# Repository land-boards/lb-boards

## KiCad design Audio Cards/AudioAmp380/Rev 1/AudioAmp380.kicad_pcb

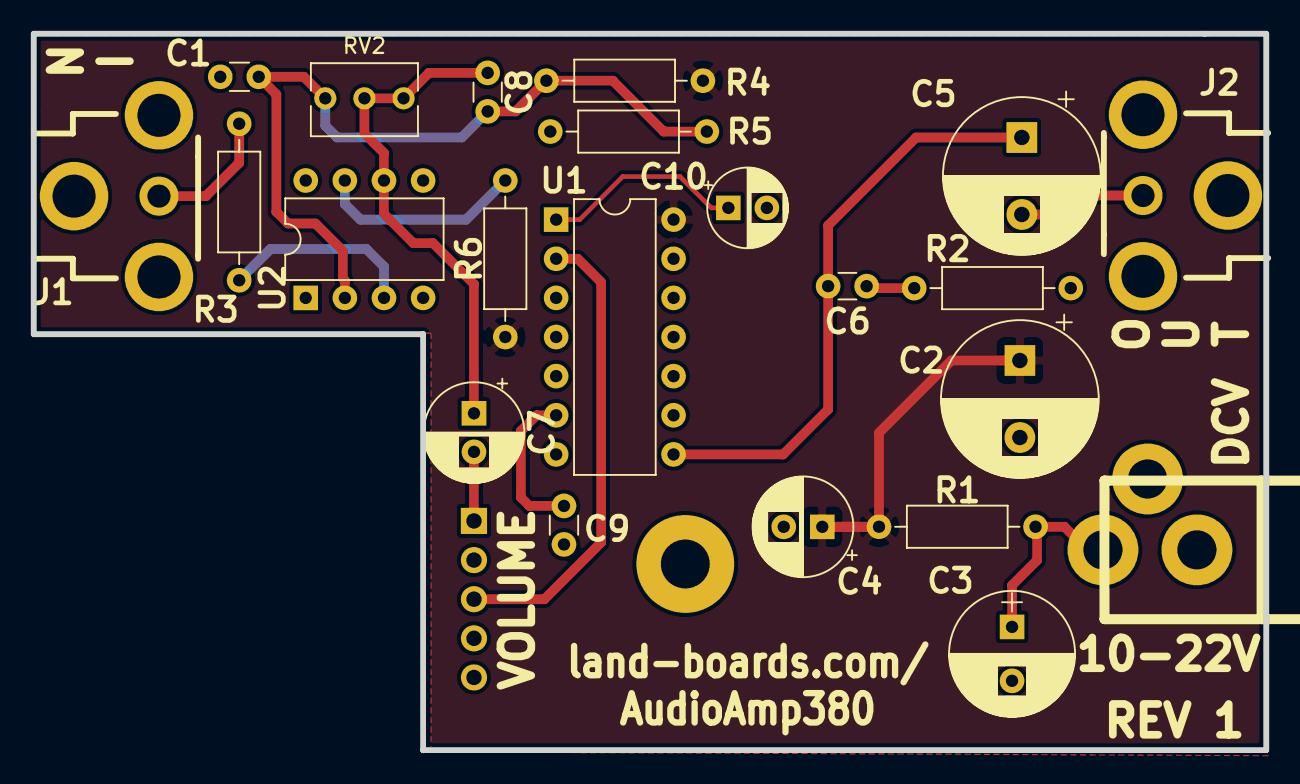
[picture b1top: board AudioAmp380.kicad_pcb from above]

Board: 2 copper layers, 80.0 x 46.5 mm, 25 parts (1 on the bottom side), 15 nets.

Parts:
C1, C8, C9: 0.1 uF; C_Disc_D3.0mm_W1.6mm_P2.50mm
C2, C5: 470uF; CP_Radial_D10.0mm_P5.00mm
C3: 100uF; CP_Radial_D8.0mm_P3.50mm
C4: 1 uF; CP_Radial_D6.3mm_P2.50mm
C6: 100uF; C_Disc_D3.0mm_W1.6mm_P2.50mm
C7: 10 uF; CP_Radial_D6.3mm_P2.50mm
C10: 4.7uF; CP_Radial_D5.0mm_P2.50mm
J1, J2: RCA-JACK; RCA
J3: DCJ0202; DCJ-NEW
MTG4: MTG_HOLE; MTG-4-40
R1, R6: 10; R_Axial_DIN0207_L6.3mm_D2.5mm_P10.16mm_Horizontal
R2: 2.7; R_Axial_DIN0207_L6.3mm_D2.5mm_P10.16mm_Horizontal
R3: 51; R_Axial_DIN0207_L6.3mm_D2.5mm_P10.16mm_Horizontal
R4, R5: 10K; R_Axial_DIN0207_L6.3mm_D2.5mm_P10.16mm_Horizontal
RV1: CONN_01X05; Pin_Header_Angled_1x05_Pitch2.54mm
RV2: 500; Potentiometer_Bourns_3266Y_Vertical
TESTED: COUPON; TEST_BLK-REAR
U1: LM380N; DIP-14_W7.62mm
U2: NE5534; DIP-8_W7.62mm

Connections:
/12VF: C2.1, C4.1, R1.1, R4.1, R6.1, U1.14
/+12V: C3.1, J3.1, R1.2
/AO: C5.1, C6.1, U1.8
/COMP: C6.2, R2.1
/IN: J1.4, R3.1
/OUT: C5.2, J2.4
/RESHI: C7.2, RV1.1
/RESWI: RV1.3, U1.2
GND: C1.2, C2.2, C3.2, C4.2, C9.1, C10.2, J1.1, J1.2, J1.3, J2.1, J2.2, J2.3, J3.2, J3.3, R2.2, R5.2, RV1.5, U1.3, U1.4, U1.5, U1.7, U1.10, U1.11, U1.12, U2.4
unnamed: C1.1, C8.2, R4.2, R5.1, RV2.3, U2.2
unnamed: C7.1, C8.1, RV2.1, RV2.2, U2.6
unnamed: C9.2, U1.6
unnamed: C10.1, U1.1
unnamed: R3.2, U2.3
unnamed: R6.2, U2.7

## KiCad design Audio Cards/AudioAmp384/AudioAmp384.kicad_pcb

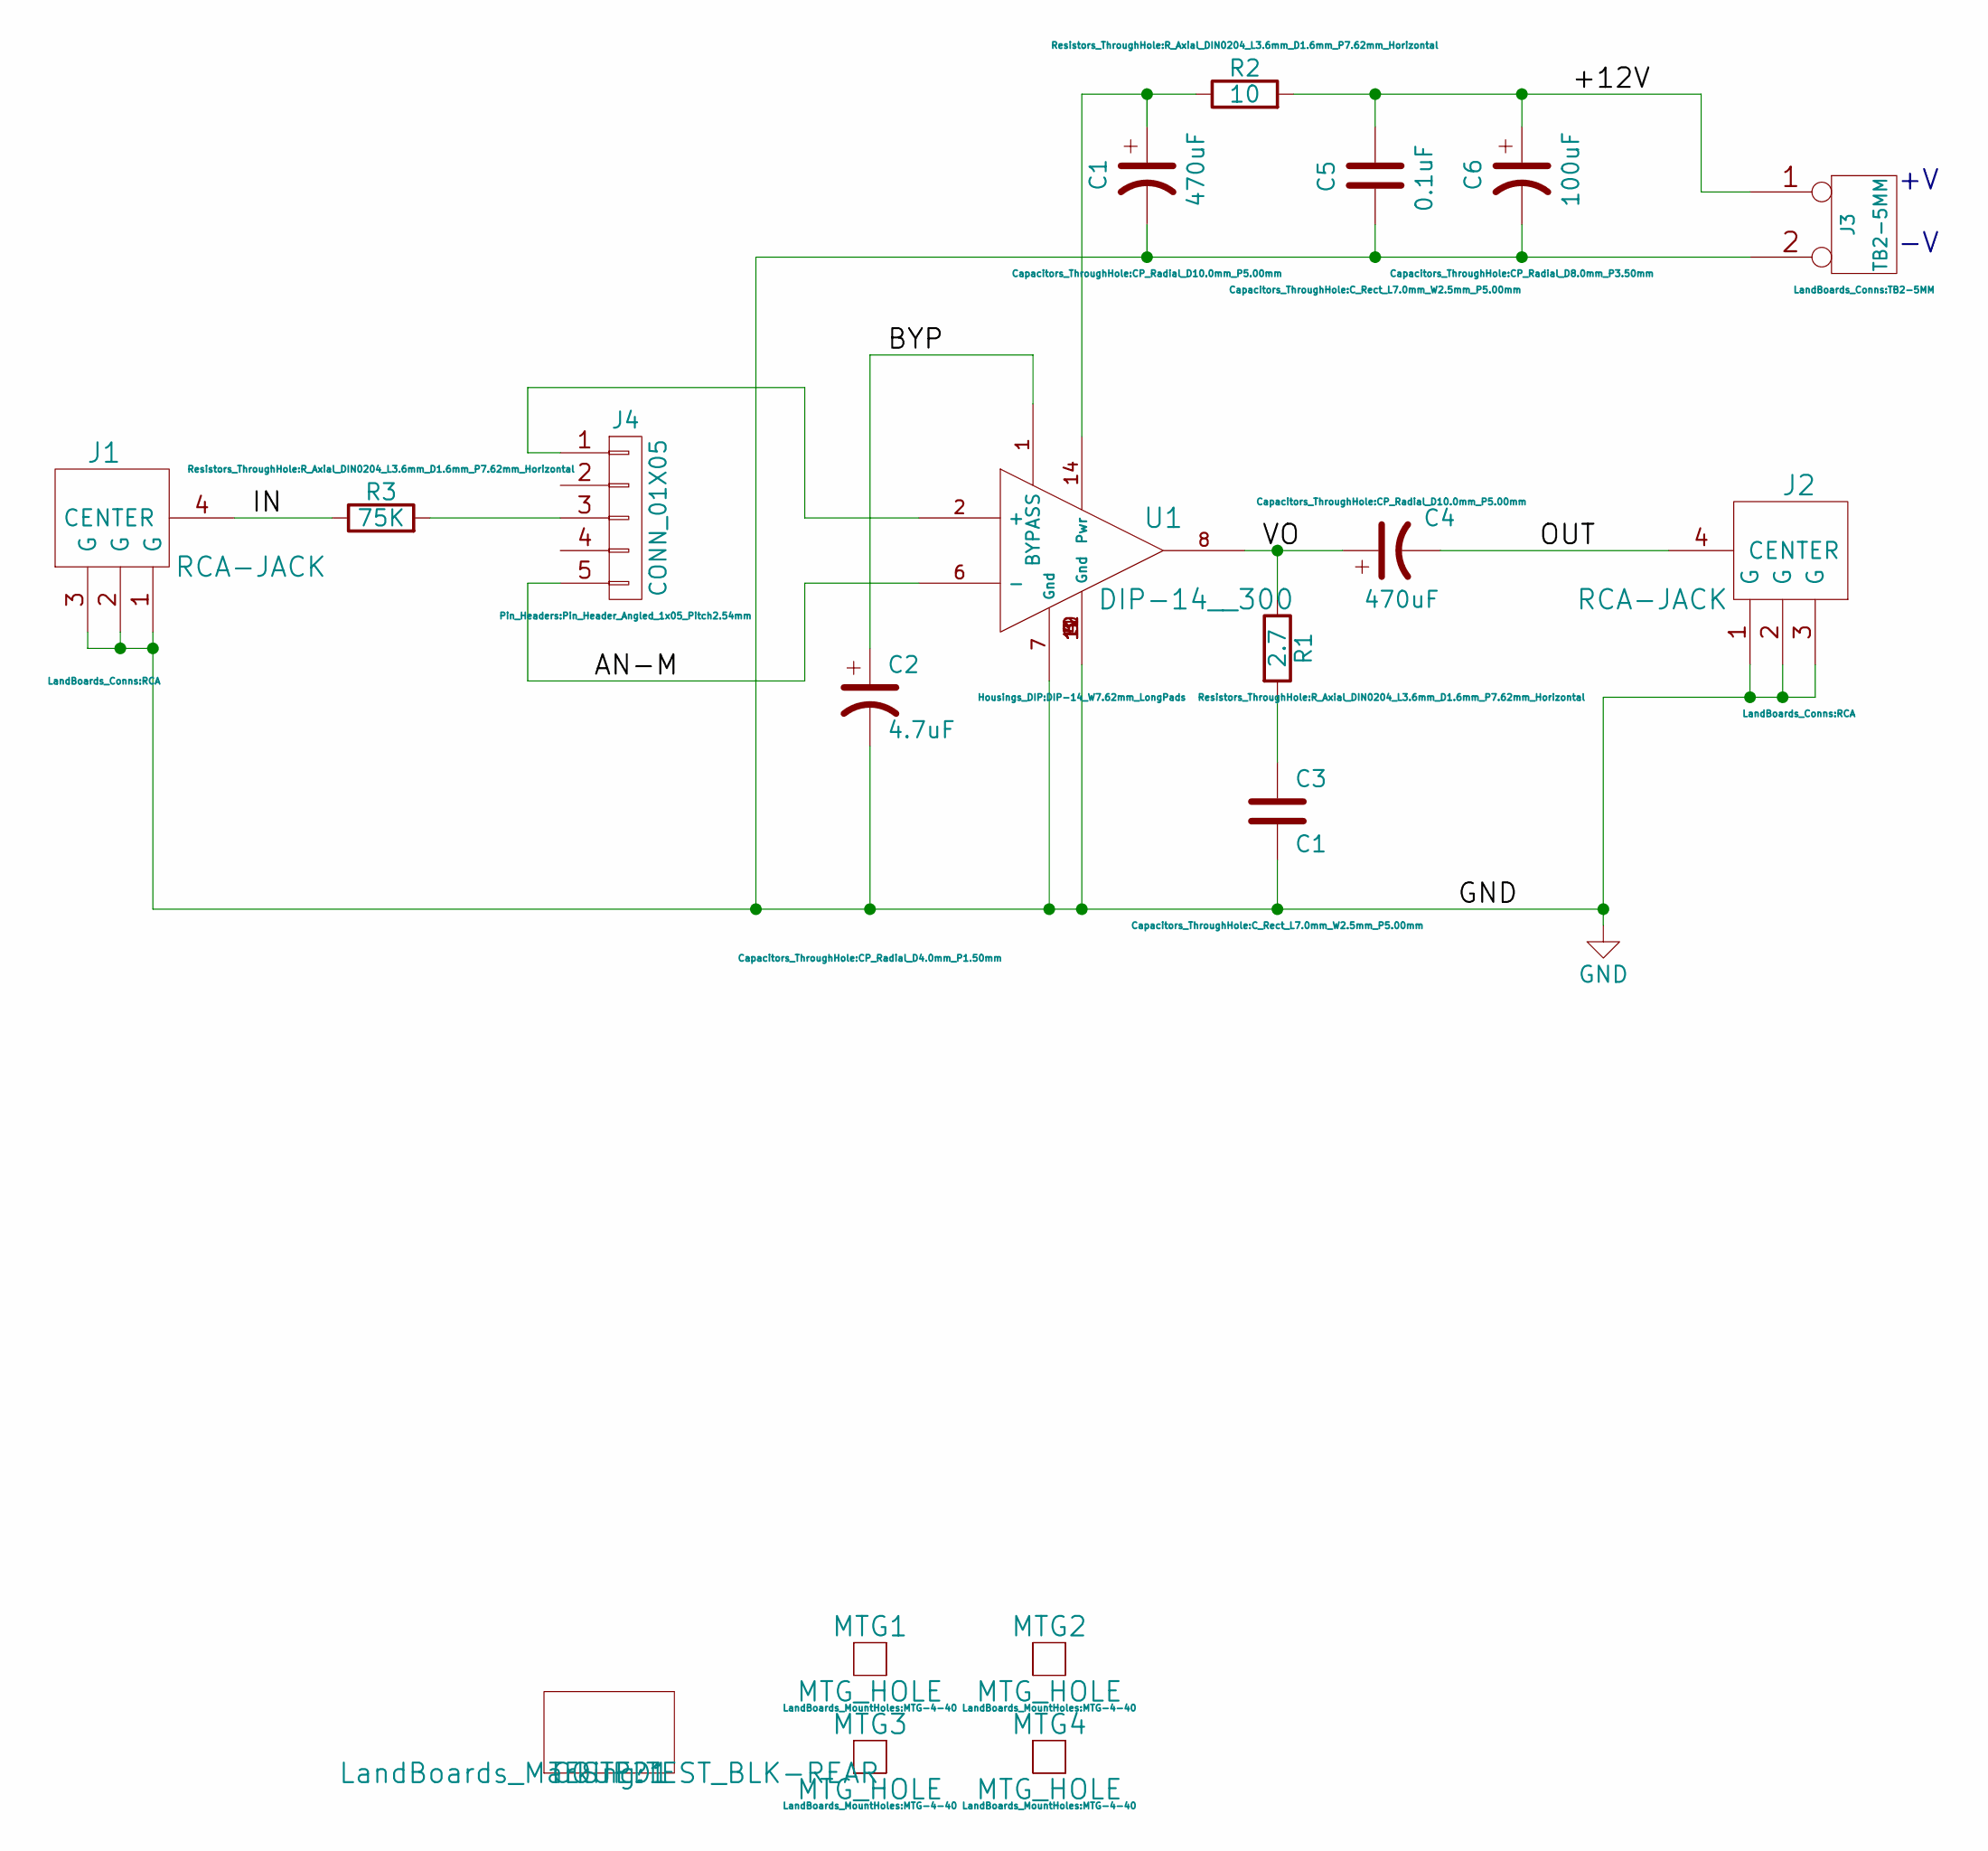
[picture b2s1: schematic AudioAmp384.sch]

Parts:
C1, C4: 470uF; CP_Radial_D10.0mm_P5.00mm
C2: 4.7uF; CP_Radial_D4.0mm_P1.50mm
C3: C1; C_Rect_L7.0mm_W2.5mm_P5.00mm
C5: 0.1uF; C_Rect_L7.0mm_W2.5mm_P5.00mm
C6: 100uF; CP_Radial_D8.0mm_P3.50mm
COUP?1: TESTED1; TEST_BLK-REAR
J1, J2: RCA-JACK; RCA
J3: TB2-5MM
J4: CONN_01X05; Pin_Header_Angled_1x05_Pitch2.54mm
MTG1, MTG2, MTG3, MTG4: MTG_HOLE; MTG-4-40
R1: 2.7; R_Axial_DIN0204_L3.6mm_D1.6mm_P7.62mm_Horizontal
R2: 10; R_Axial_DIN0204_L3.6mm_D1.6mm_P7.62mm_Horizontal
R3: 75K; R_Axial_DIN0204_L3.6mm_D1.6mm_P7.62mm_Horizontal
U1: DIP-14__300; DIP-14_W7.62mm_LongPads

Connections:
/+12V: C5.2, C6.1, J3.1, R2.2
/AN-M: J4.5, U1.6 (-)
/BYP: C2.1, U1.1 (BYPASS)
/IN: J1.4 (CENTER), R3.1
/OUT: C4.2, J2.4 (CENTER)
/VO: C4.1, R1.1, U1.8
GND: C1.2, C2.2, C3.2, C5.1, C6.2, J1.1 (G), J1.2 (G), J1.3 (G), J2.1 (G), J2.2 (G), J2.3 (G), J3.2 (PM), U1.3 (Gnd), U1.4 (Gnd), U1.5 (Gnd), U1.7 (Gnd), U1.10 (Gnd), U1.11 (Gnd), U1.12 (Gnd)
unnamed: C1.1, R2.1, U1.14 (Pwr)
unnamed: C3.1, R1.2
unnamed: J4.1, U1.2 (+)
unnamed: J4.3, R3.2

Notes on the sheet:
+V -V

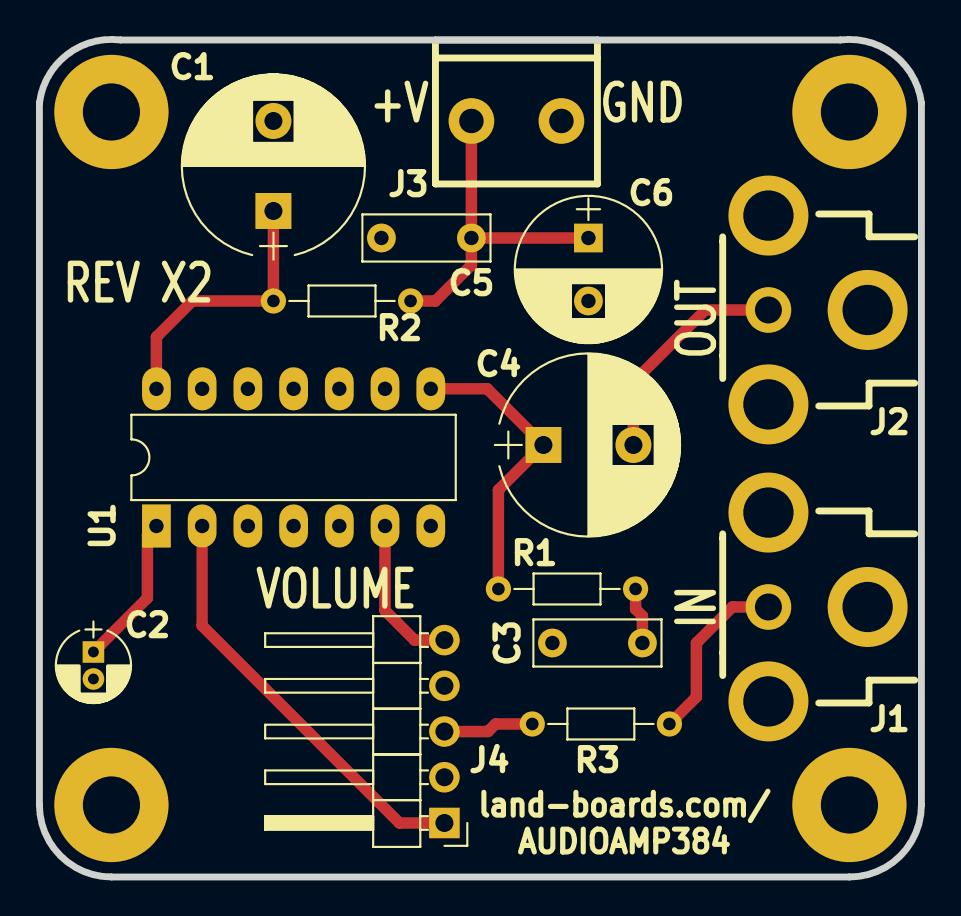
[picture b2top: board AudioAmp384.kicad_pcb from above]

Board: 2 copper layers, 49.0 x 46.5 mm, 19 parts (0 on the bottom side), 11 nets.

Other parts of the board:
TESTED: TESTED1; TEST_BLK-REAR

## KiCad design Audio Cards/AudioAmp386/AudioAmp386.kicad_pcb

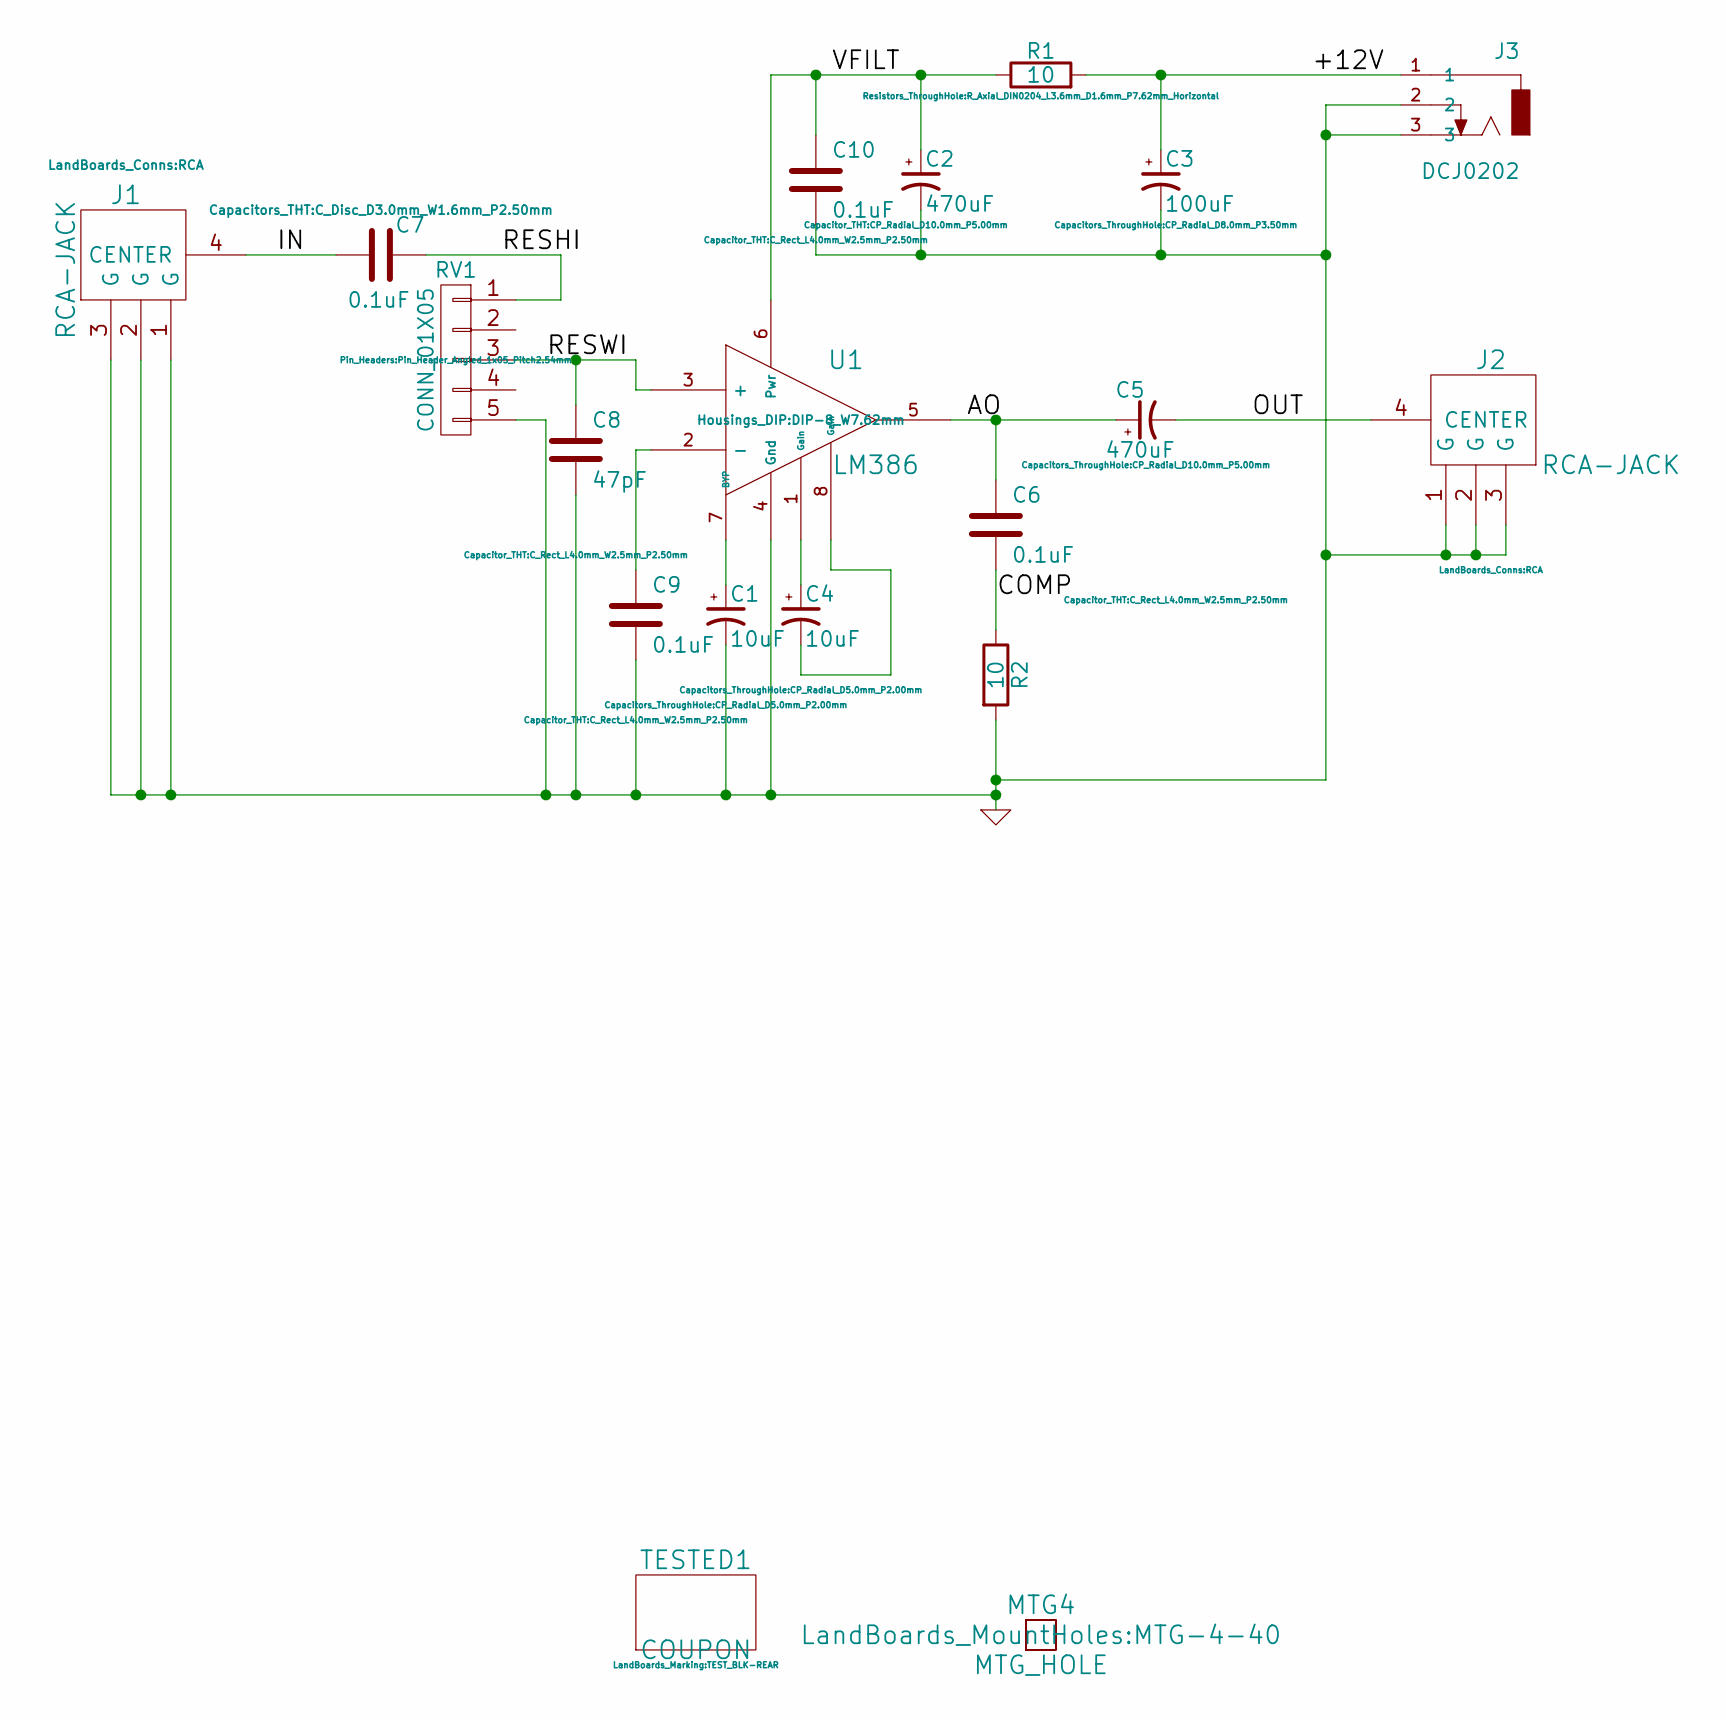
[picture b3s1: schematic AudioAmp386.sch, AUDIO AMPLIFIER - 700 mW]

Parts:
C1, C4: 10uF; CP_Radial_D5.0mm_P2.00mm
C2, C5: 470uF; CP_Radial_D10.0mm_P5.00mm
C3: 100uF; CP_Radial_D8.0mm_P3.50mm
C6, C9, C10: 0.1uF; C_Rect_L4.0mm_W2.5mm_P2.50mm
C7: 0.1uF; C_Disc_D3.0mm_W1.6mm_P2.50mm; MfgPN 1C10Z5U104M050B
C8: 47pF; C_Rect_L4.0mm_W2.5mm_P2.50mm
J1, J2: RCA-JACK; RCA; MfgPN NYS354
J3: DCJ0202; DCJ-NEW
MTG4: MTG_HOLE; MTG-4-40
R1: 10; R_Axial_DIN0204_L3.6mm_D1.6mm_P7.62mm_Horizontal
R2: 10; R_Axial_DIN0204_L3.6mm_D1.6mm_P7.62mm_Horizontal; MfgPN CCF0710R0GKE36
RV1: CONN_01X05; Pin_Header_Angled_1x05_Pitch2.54mm
TESTED1: COUPON; TEST_BLK-REAR
U1: LM386; DIP-8_W7.62mm; MfgPN LM386N-3/NOPB

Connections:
/+12V: C3.1, J3.1, R1.2
/AO: C5.1, C6.1, U1.5
/COMP: C6.2, R2.1
/IN: C7.1, J1.4 (CENTER)
/OUT: C5.2, J2.4 (CENTER)
/RESHI: C7.2, RV1.1
/RESWI: C8.1, RV1.3, U1.3 (+)
/VFILT: C2.1, C10.1, R1.1, U1.6 (Pwr)
GND: C1.2, C2.2, C3.2, C8.2, C9.2, C10.2, J1.1 (G), J1.2 (G), J1.3 (G), J2.1 (G), J2.2 (G), J2.3 (G), J3.2, J3.3, R2.2, RV1.5, U1.4 (Gnd)
unnamed: C1.1, U1.7 (BYP)
unnamed: C4.1, U1.1 (Gain)
unnamed: C4.2, U1.8 (Gain)
unnamed: C9.1, U1.2 (-)

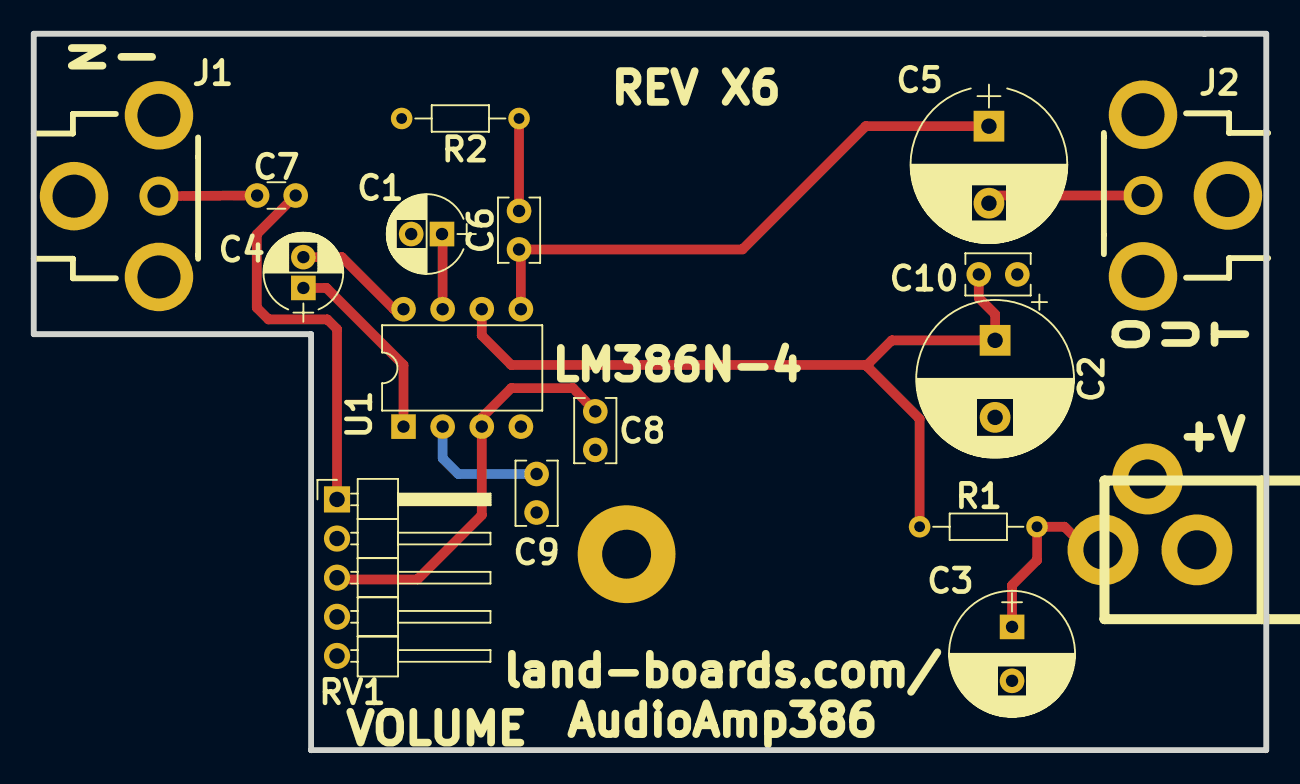
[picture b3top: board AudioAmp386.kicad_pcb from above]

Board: 2 copper layers, 80.0 x 46.5 mm, 19 parts (0 on the bottom side), 13 nets.

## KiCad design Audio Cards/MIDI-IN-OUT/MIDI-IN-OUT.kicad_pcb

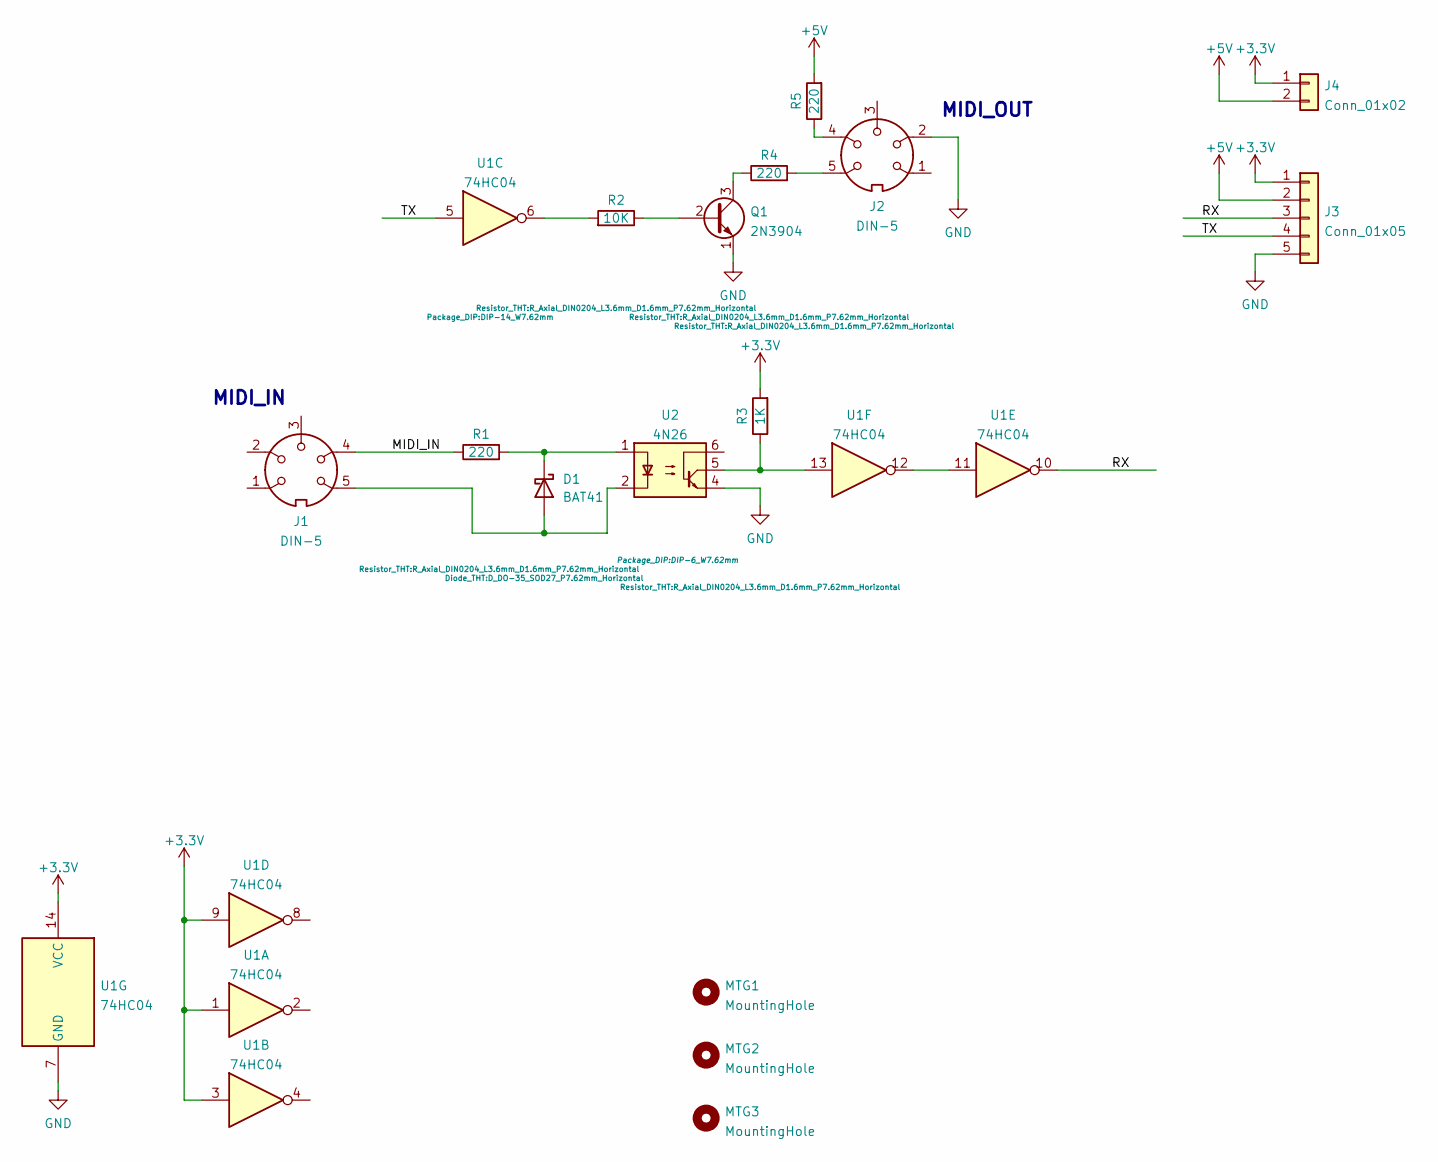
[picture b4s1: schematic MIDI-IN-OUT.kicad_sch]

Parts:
D1: BAT41; D_DO-35_SOD27_P7.62mm_Horizontal
J1, J2: DIN-5; MIDI_DIN-5
J3: Conn_01x05; PinHeader_1x05_P2.54mm_Horizontal
J4: Conn_01x02; PinHeader_1x02_P2.54mm_Vertical
MTG1, MTG2, MTG3: MountingHole; MTG-4-40-SMALL
Q1: 2N3904; TO-92_Inline
R1, R4, R5: 220; R_Axial_DIN0204_L3.6mm_D1.6mm_P7.62mm_Horizontal
R2: 10K; R_Axial_DIN0204_L3.6mm_D1.6mm_P7.62mm_Horizontal
R3: 1K; R_Axial_DIN0204_L3.6mm_D1.6mm_P7.62mm_Horizontal
U1: 74HC04
U2: 4N26; DIP-6_W7.62mm

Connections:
+3V3: J3.1, J4.1, R3.2, U1.1, U1.3, U1.9, U1.14 (VCC)
+5V: J3.2, J4.2, R5.2
/MIDI_IN: J1.4, R1.1
/RX: J3.3, U1.10
/TX: J3.4, U1.5
GND: J2.2, J3.5, Q1.1 (E), U1.7 (GND), U2.4
unnamed: D1.1 (K), R1.2, U2.1
unnamed: D1.2 (A), J1.5, U2.2
unnamed: J2.4, R5.1
unnamed: J2.5, R4.2
unnamed: Q1.2 (B), R2.1
unnamed: Q1.3 (C), R4.1
unnamed: R2.2, U1.6
unnamed: R3.1, U1.13, U2.5
unnamed: U1.11, U1.12

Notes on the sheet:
MIDI_IN
MIDI_OUT

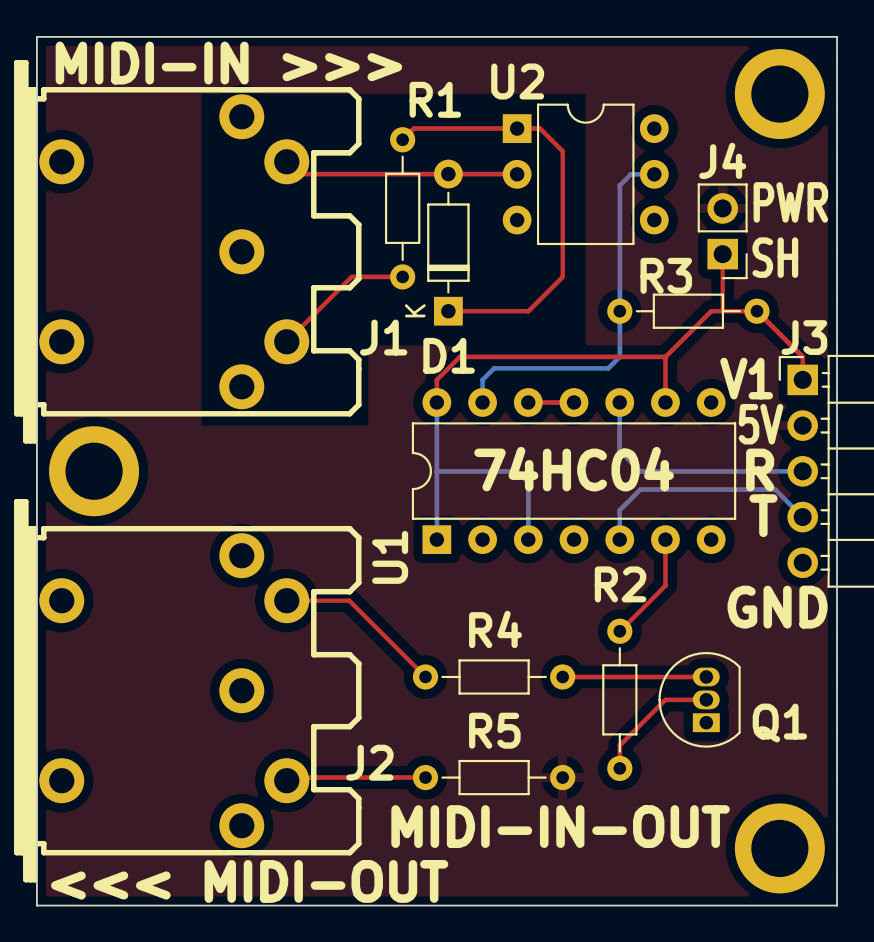
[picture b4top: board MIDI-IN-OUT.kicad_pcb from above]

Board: 2 copper layers, 44.4 x 48.3 mm, 16 parts (0 on the bottom side), 15 nets.

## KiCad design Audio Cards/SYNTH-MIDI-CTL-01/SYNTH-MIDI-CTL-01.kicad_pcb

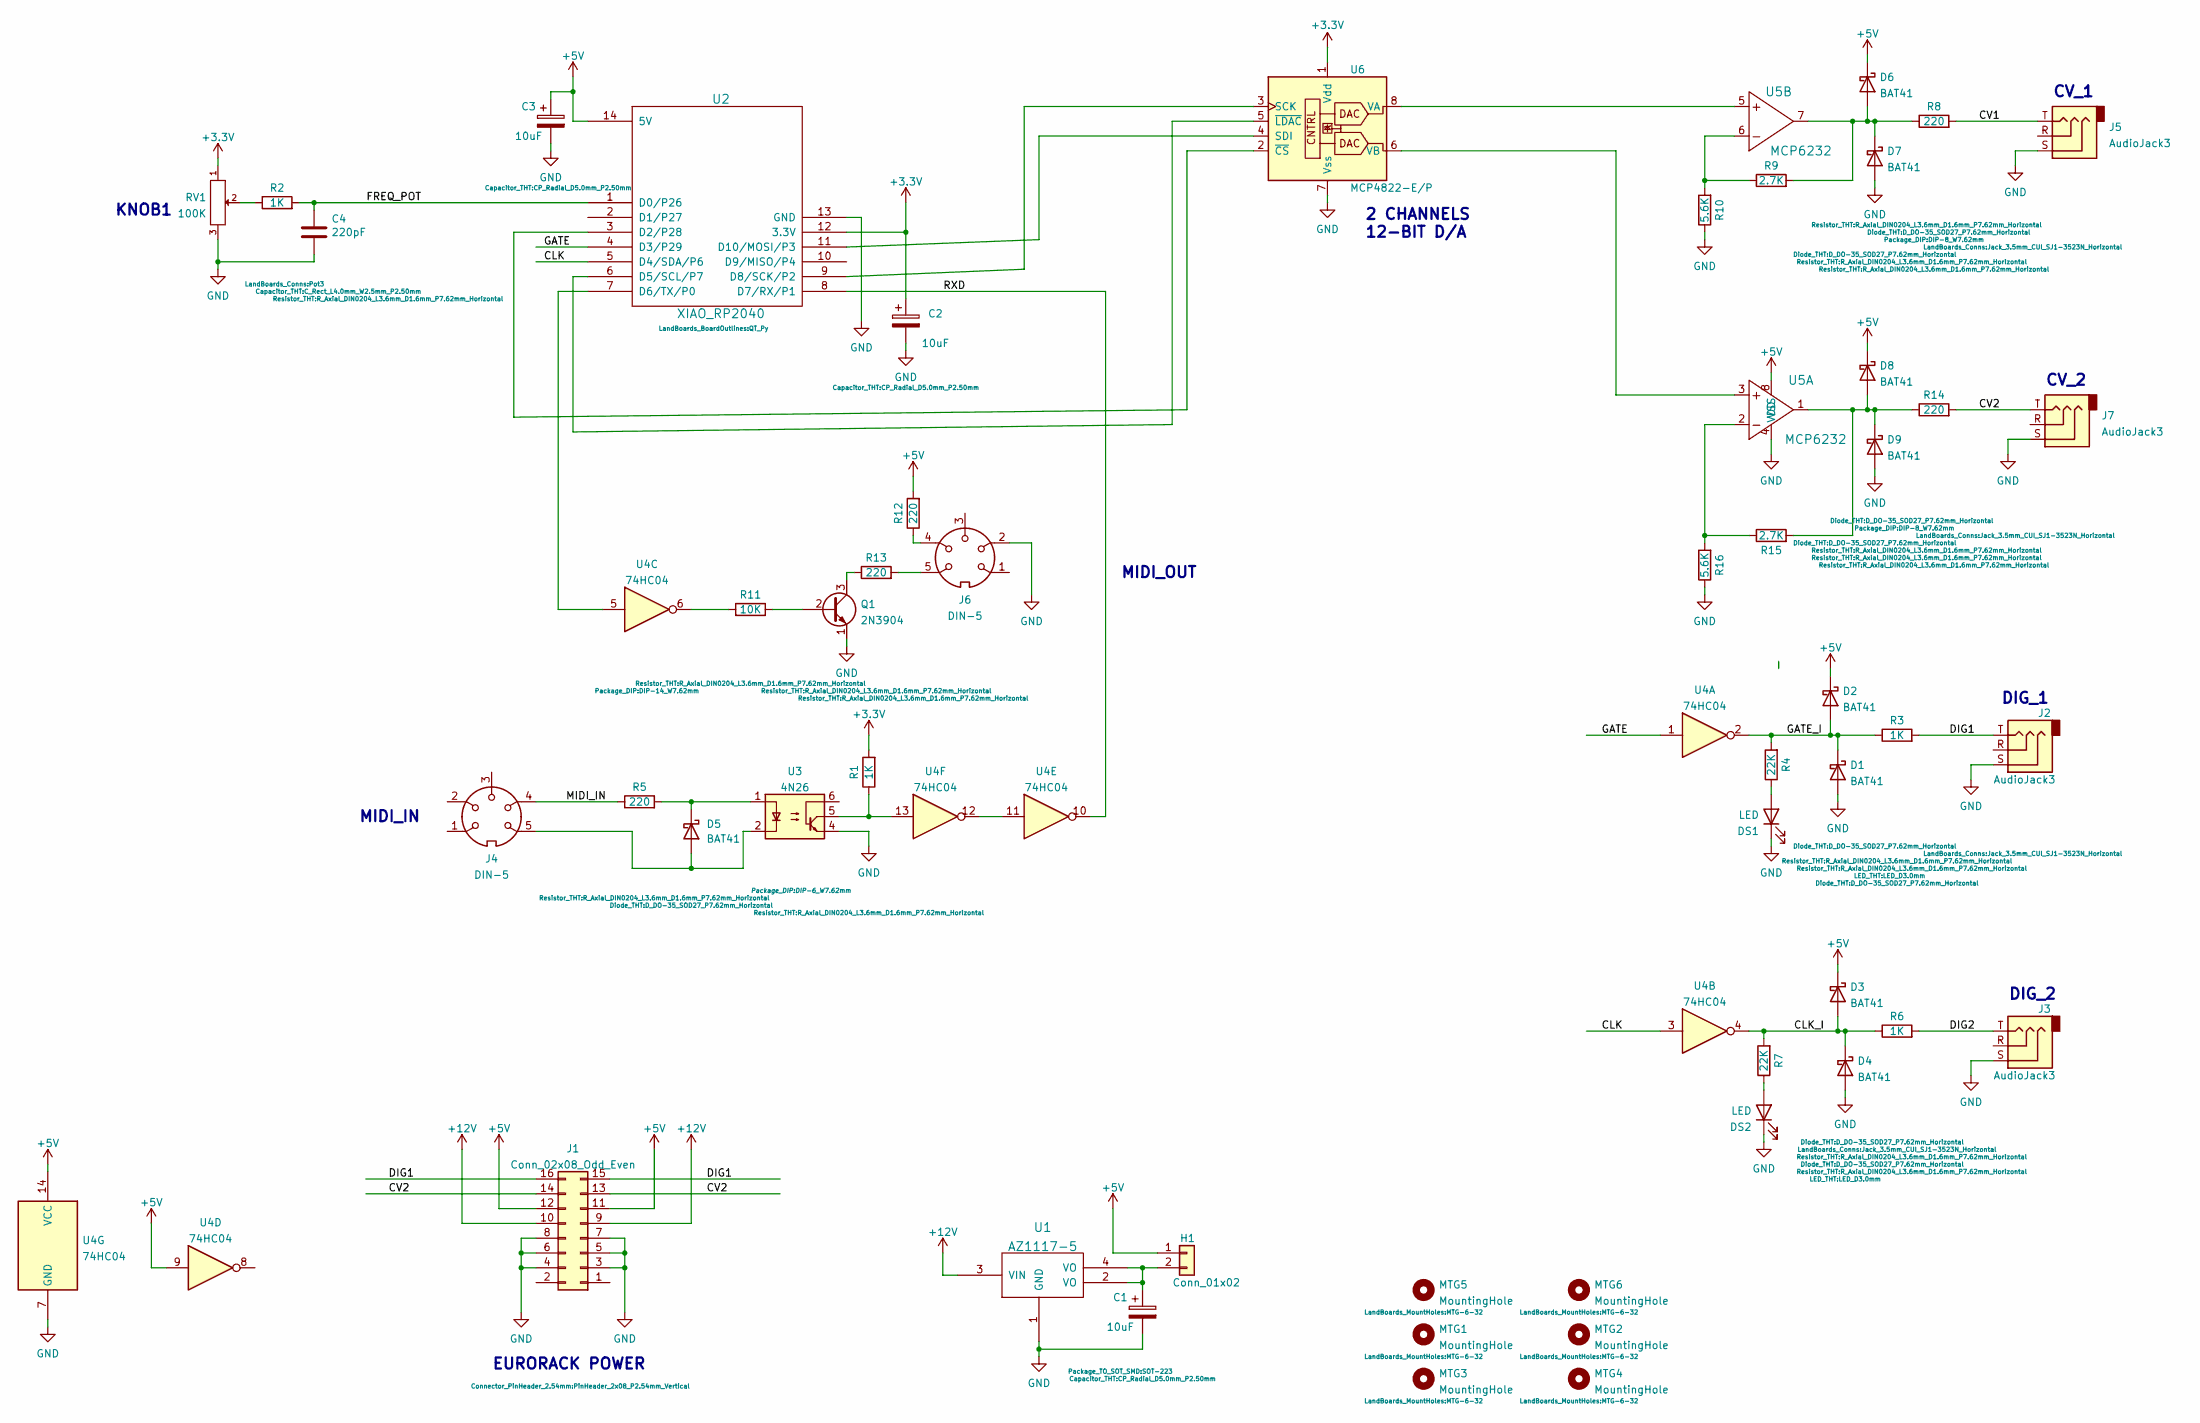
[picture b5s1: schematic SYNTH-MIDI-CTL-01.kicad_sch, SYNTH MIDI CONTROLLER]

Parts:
C1, C2, C3: 10uF; CP_Radial_D5.0mm_P2.50mm
C4: 220pF; C_Rect_L4.0mm_W2.5mm_P2.50mm
D1, D2, D3, D4, D5, D6, D7, D8, D9: BAT41; D_DO-35_SOD27_P7.62mm_Horizontal
DS1, DS2: LED; LED_D3.0mm
H1: Conn_01x02; PinHeader_1x02_P2.54mm_Vertical
J1: Conn_02x08_Odd_Even; PinHeader_2x08_P2.54mm_Vertical
J2, J3, J5, J7: AudioJack3; Jack_3.5mm_CUI_SJ1-3523N_Horizontal
J4, J6: DIN-5; MIDI_DIN-5
MTG1, MTG2, MTG3, MTG4, MTG5, MTG6: MountingHole; MTG-6-32
Q1: 2N3904; TO-92_Inline
R1, R2, R3, R6: 1K; R_Axial_DIN0204_L3.6mm_D1.6mm_P7.62mm_Horizontal
R4, R7: 22K; R_Axial_DIN0204_L3.6mm_D1.6mm_P7.62mm_Horizontal
R5, R8, R12, R13, R14: 220; R_Axial_DIN0204_L3.6mm_D1.6mm_P7.62mm_Horizontal
R9, R15: 2.7K; R_Axial_DIN0204_L3.6mm_D1.6mm_P7.62mm_Horizontal
R10, R16: 5.6K; R_Axial_DIN0204_L3.6mm_D1.6mm_P7.62mm_Horizontal
R11: 10K; R_Axial_DIN0204_L3.6mm_D1.6mm_P7.62mm_Horizontal
RV1: 100K; Pot3
U1: AZ1117-5; SOT-223
U2: XIAO_RP2040; QT_Py
U3: 4N26; DIP-6_W7.62mm
U4: 74HC04
U5: MCP6232; DIP-8_W7.62mm
U6: MCP4822-E/P; DIP-8_W7.62mm

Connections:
+3V3: C2.1, R1.2, RV1.1, U2.12 (3.3V), U6.1 (Vdd)
+5V: C3.1, D2.1 (K), D3.1 (K), D6.1 (K), D8.1 (K), H1.1, J1.11, J1.12, R12.2, U2.14 (5V), U4.9, U4.14 (VCC), U5.8 (VDD)
+12V: J1.9, J1.10, U1.3 (VIN)
/CLK: U2.5 (D4/SDA/P6), U4.3
/CLK_I: D3.2 (A), D4.1 (K), R6.1, R7.2, U4.4
/CV1: J5.T, R8.2
/CV2: J1.13, J1.14, J7.T, R14.2
/DIG1: J1.15, J1.16, J2.T, R3.2
/DIG2: J3.T, R6.2
/FREQ_POT: C4.1, R2.2, U2.1 (D0/P26)
/GATE: U2.4 (D3/P29), U4.1
/GATE_I: D1.1 (K), D2.2 (A), R3.1, R4.2, U4.2
/MIDI_IN: J4.4, R5.1
/RXD: U2.8 (D7/RX/P1), U4.10
GND: C1.2, C2.2, C3.2, C4.2, D1.2 (A), D4.2 (A), D7.2 (A), D9.2 (A), DS1.1 (K), DS2.1 (K), J1.3, J1.4, J1.5, J1.6, J1.7, J1.8, J2.S, J3.S, J5.S, J6.2, J7.S, Q1.1 (E), R10.1, R16.1, RV1.3, U1.1 (GND), U2.13 (GND), U3.4, U4.7 (GND), U5.4 (VSS), U6.7 (Vss)
unnamed: C1.1, H1.2, U1.2 (VO), U1.4 (VO)
unnamed: D5.1 (K), R5.2, U3.1
unnamed: D5.2 (A), J4.5, U3.2
unnamed: D6.2 (A), D7.1 (K), R8.1, R9.2, U5.7 (Q)
unnamed: D8.2 (A), D9.1 (K), R14.1, R15.2, U5.1 (Q)
unnamed: DS1.2 (A), R4.1
unnamed: DS2.2 (A), R7.1
unnamed: J6.4, R12.1
unnamed: J6.5, R13.2
unnamed: Q1.2 (B), R11.1
unnamed: Q1.3 (C), R13.1
unnamed: R1.1, U3.5, U4.13
unnamed: R2.1, RV1.2
unnamed: R9.1, R10.2, U5.6 (-)
unnamed: R11.2, U4.6
unnamed: R15.1, R16.2, U5.2 (-)
unnamed: U2.3 (D2/P28), U6.2 (~CS)
unnamed: U2.6 (D5/SCL/P7), U6.5 (~LDAC)
unnamed: U2.7 (D6/TX/P0), U4.5
unnamed: U2.9 (D8/SCK/P2), U6.3 (SCK)
unnamed: U2.11 (D10/MOSI/P3), U6.4 (SDI)
unnamed: U4.11, U4.12
unnamed: U5.3 (+), U6.6 (VB)
unnamed: U5.5 (+), U6.8 (VA)

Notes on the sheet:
CV_2
DIG_1
MIDI_IN
2 CHANNELS 12-BIT D/A
KNOB1
MIDI_OUT
DIG_2
CV_1
EURORACK POWER

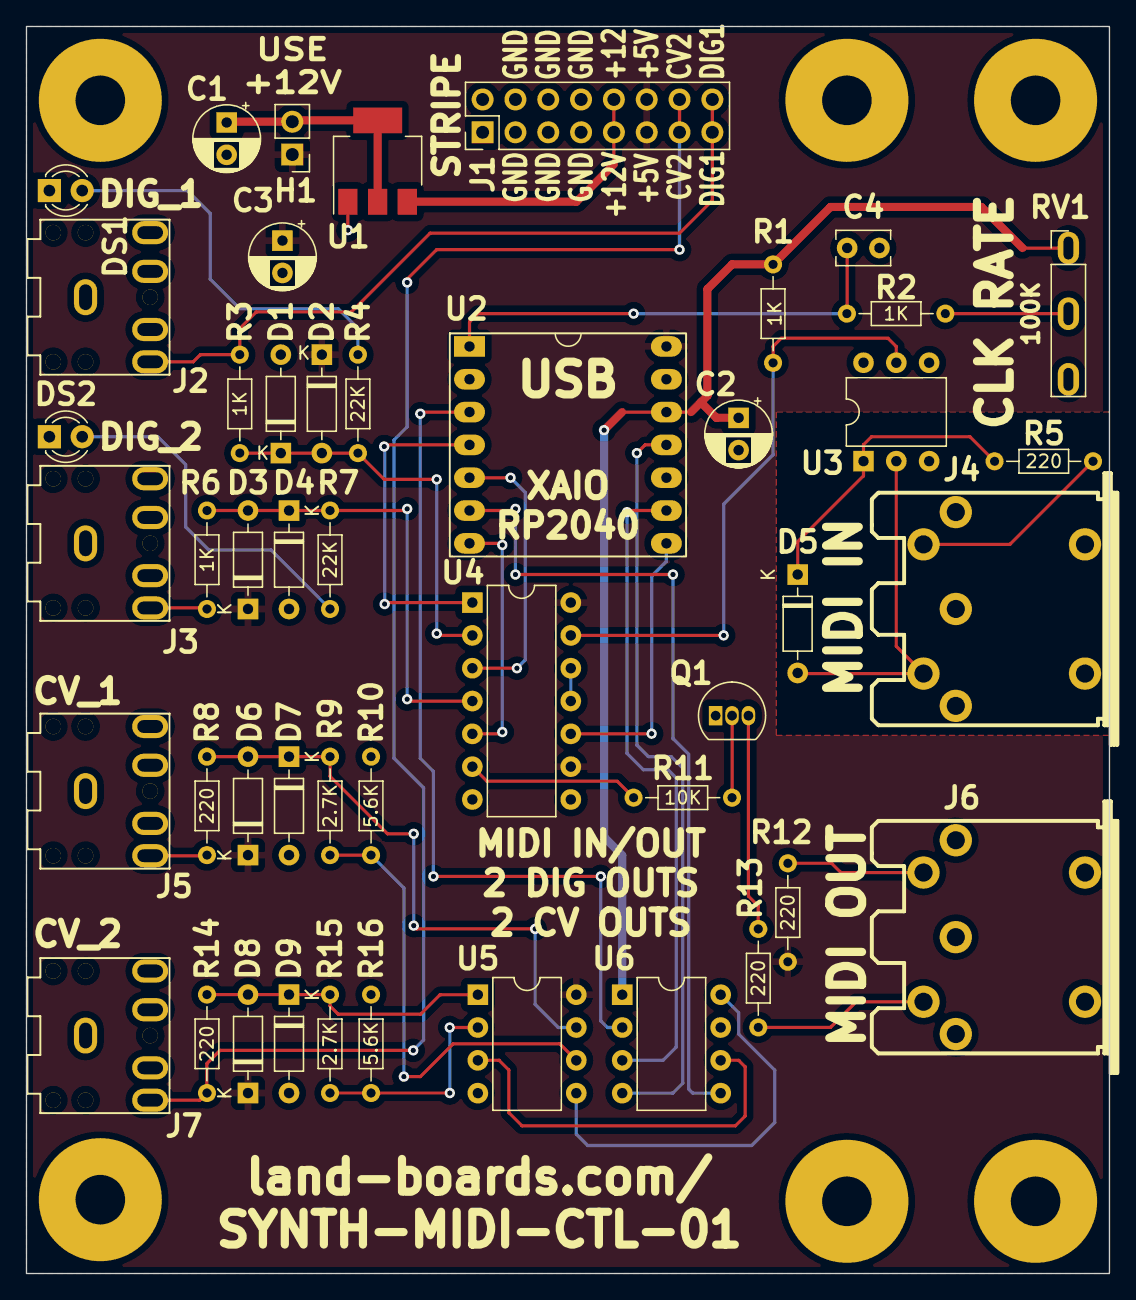
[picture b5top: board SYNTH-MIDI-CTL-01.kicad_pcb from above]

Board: 2 copper layers, 83.8 x 96.5 mm, 53 parts (0 on the bottom side), 39 nets.
